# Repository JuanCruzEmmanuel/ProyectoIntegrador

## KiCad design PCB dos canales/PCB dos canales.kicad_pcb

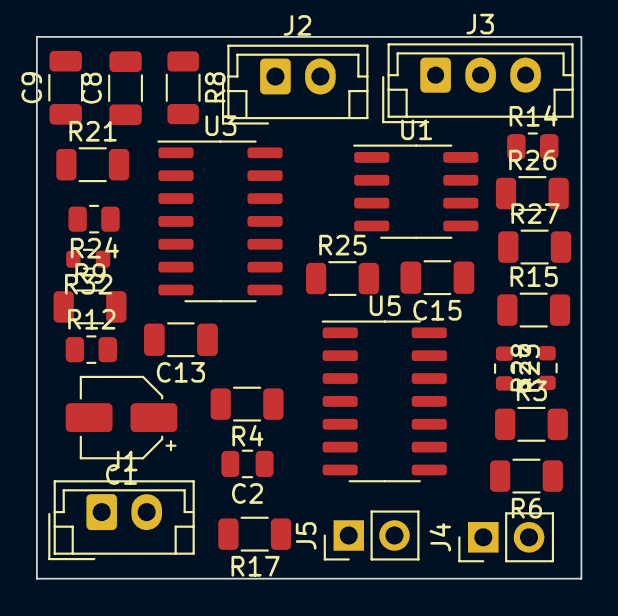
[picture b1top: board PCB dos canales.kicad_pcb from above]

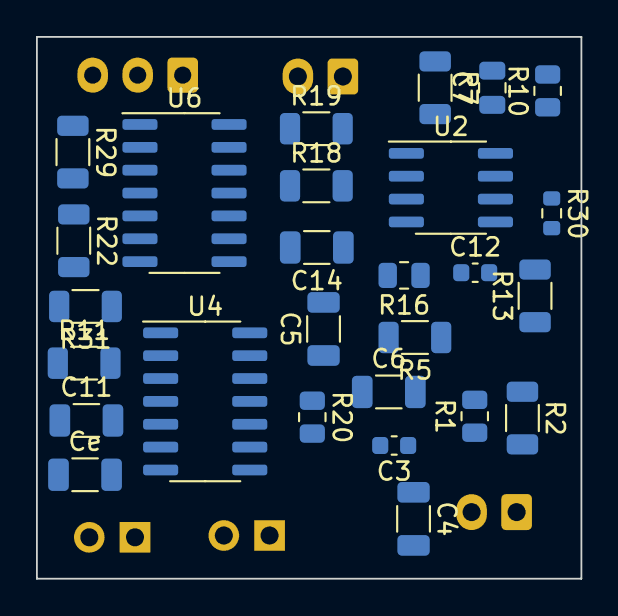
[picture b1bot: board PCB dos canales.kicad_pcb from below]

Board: 2 copper layers, 30.3 x 30.1 mm, 58 parts (27 on the bottom side), 45 nets, no tracks yet.

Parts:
C1: 47uF; CP_Elec_4x4.5
C2, C7: 47nF; C_0805_2012Metric
C3, C12: 100nF; C_0603_1608Metric
C4, C13: 220nF; C_1206_3216Metric
C5, C6, C8, C9: 1nF; C_1206_3216Metric
C11, C14, C15: 1uF; C_1206_3216Metric
Ce: 1uF; C_1206_3216Metric
J1, J2: Conn_01x02; JST_EH_B2B-EH-A_1x02_P2.50mm_Vertical
J3: Conn_01x03; JST_EH_B3B-EH-A_1x03_P2.50mm_Vertical
J4, J5: Conn_01x02; PinHeader_1x02_P2.54mm_Vertical
R1: 3.3M; R_0805_2012Metric
R2: 2.2M; R_1206_3216Metric
R3, R6, R9, R13: 39K; R_1206_3216Metric
R4, R5, R7, R8, R17, R21: 4.7K; R_1206_3216Metric
R10, R14: 8K; R_0805_2012Metric
R11, R15, R25, R31: 1M; R_1206_3216Metric
R12, R16: 470K; R_0805_2012Metric
R18, R19, R26, R27: 100K; R_1206_3216Metric
R20, R24: 70K; R_0805_2012Metric
R22, R29: 560K; R_1206_3216Metric
R23, R28, R30, R32: 1.5K; R_0603_1608Metric
U1, U2: AD620; SOIC-8_3.9x4.9mm_P1.27mm
U3, U4, U5, U6: LM324; SO-14_3.9x8.65mm_P1.27mm

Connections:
+V: C1.1, J1.2, R1.1, U1.7 (Vs+), U2.7 (Vs+), U3.4 (V+), U4.4 (V+), U5.4 (V+), U6.4 (V+)
-V: C1.2, J1.1, J4.2, J5.2, R2.2, U1.4 (Vs-), U2.4 (Vs-), U3.11 (V-), U4.11 (V-), U5.11 (V-), U6.11 (V-)
ElecNegHor: J3.2, R7.1
ElecNegVer: J2.1, R4.1
ElecPositHor: J3.3, R8.1
ElecPositVer: J2.2, R5.1
GND: C3.1, C5.2, C6.2, C8.2, C9.2, C12.1, R11.1, R15.1, R17.2, R21.2, R23.1, R30.1, U1.5 (Ref), U2.5 (Ref), U4.1, U4.2 (-), U4.12 (+), U6.12 (+)
unnamed: C4.2, R3.2, R6.1
unnamed: C11.2, Ce.1, R12.2
unnamed: C13.2, R9.2, R13.1
unnamed: C14.1, C15.2, R16.2
unnamed: R1.2, R2.1, U4.3 (+)
unnamed: R30.2, R32.2, U3.9 (-)
unnamed: R21.1, R24.2, U3.2 (-)
unnamed: C15.1, R15.2, U3.5 (+)
unnamed: C12.2, R13.2, U3.12 (+)
unnamed: C13.1, C14.2, U3.13 (-), U3.14
unnamed: R26.2, R27.1, U4.5 (+)
unnamed: R29.2, U4.6 (-), U4.7, U4.13 (-)
unnamed: R31.1, U4.14
unnamed: R17.1, R20.2, U5.2 (-)
unnamed: C11.1, R11.2, U5.5 (+)
unnamed: R23.2, R28.2, U5.9 (-)
unnamed: C3.2, R6.2, U5.12 (+)
unnamed: C4.1, Ce.2, U5.13 (-), U5.14
unnamed: R18.2, R19.1, U6.5 (+)
unnamed: R22.2, U6.6 (-), U6.7, U6.13 (-)
unnamed: R25.1, U6.14
OUTHor1: U1.6, U3.3 (+)
OUTHor2: R9.1, R24.1, U3.1
OUTHor3: R16.1, U3.6 (-), U3.7, U3.10 (+)
OUTHor4: J5.1, R32.1, U3.8
OUTVer1: U2.6, U5.3 (+)
OUTVer2: R3.1, R20.1, U5.1
OUTVer3: R12.1, U5.6 (-), U5.7, U5.10 (+)
OUTVer4: J4.1, R28.1, U5.8
OutNegHor: C7.2, C8.1, R7.2, U1.2 (-)
OutNegVer: C2.2, C5.1, R4.2, U2.2 (-)
OutPositHor: C7.1, C9.1, R8.2, U1.3 (+)
OutPositVer: C2.1, C6.1, R5.2, U2.3 (+)
Ref: J3.1, R22.1, R25.2, R29.1, R31.2
RgHor1: R14.2, R26.1, U1.1 (Rg)
RgHor2: R14.1, R27.2, U1.8 (Rg)
RgVer1: R10.2, R18.1, U2.1 (Rg)
RgVer2: R10.1, R19.2, U2.8 (Rg)

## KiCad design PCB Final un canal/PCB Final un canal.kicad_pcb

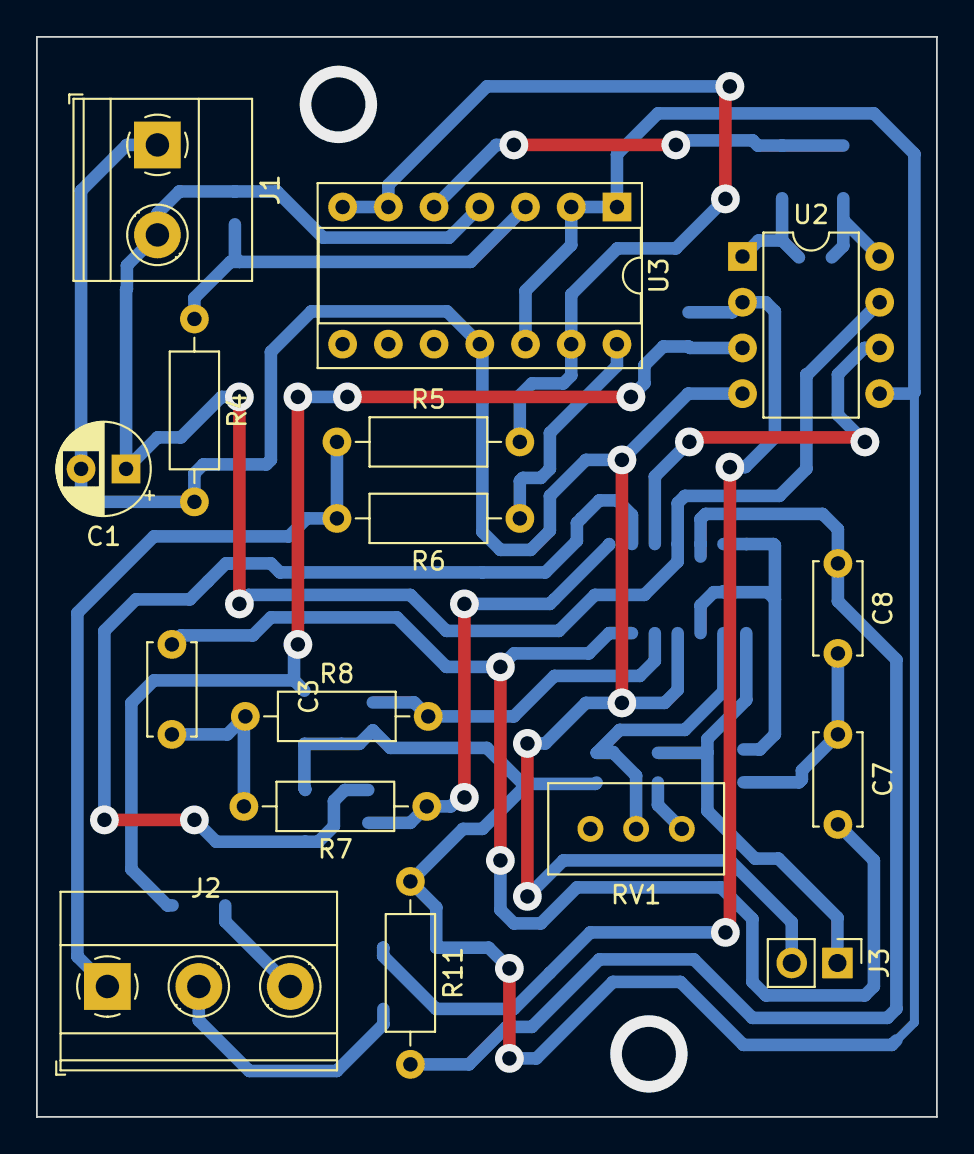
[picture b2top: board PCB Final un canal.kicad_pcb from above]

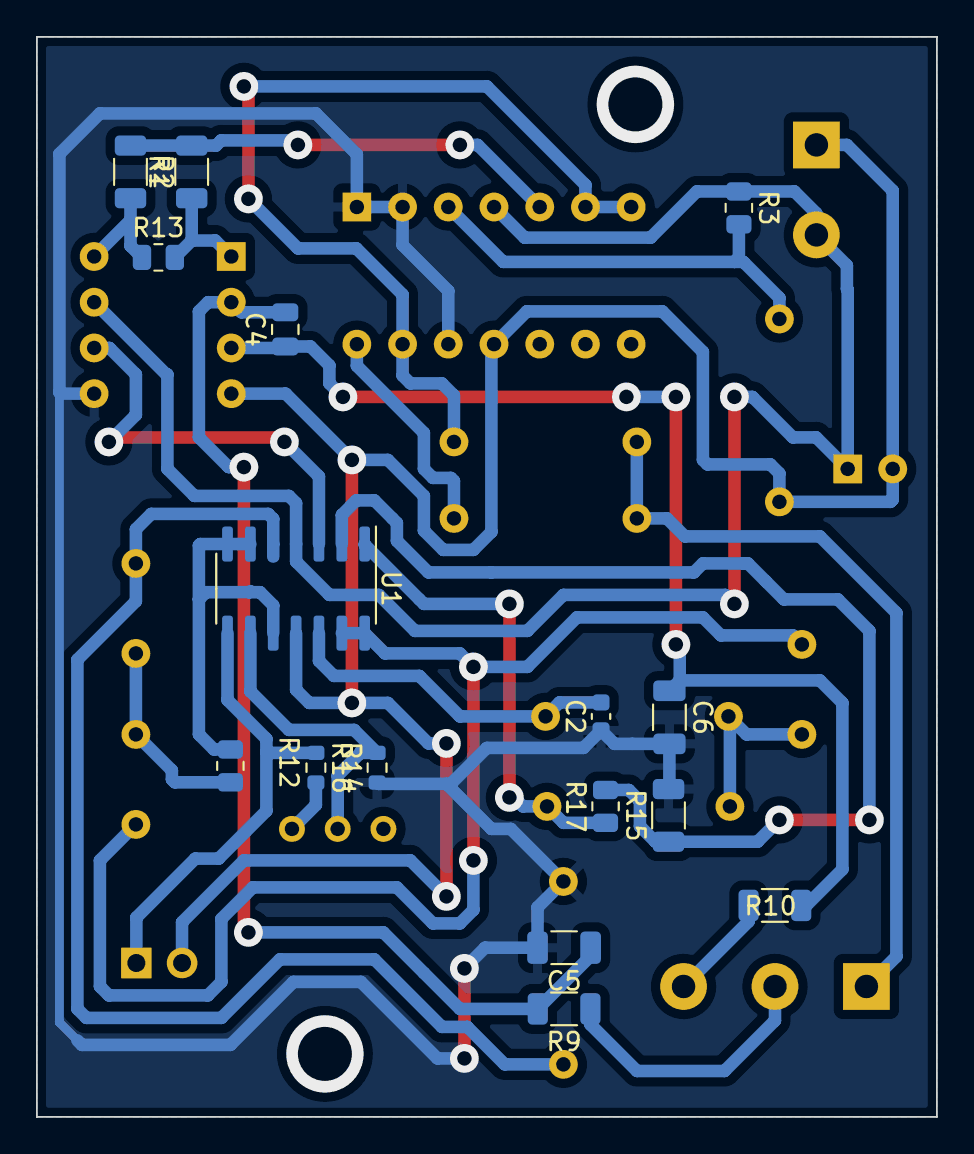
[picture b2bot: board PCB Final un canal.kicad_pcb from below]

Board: 2 copper layers, 50.0 x 60.0 mm, 32 parts (16 on the bottom side), 26 nets.

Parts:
C1: 47uF; CP_Radial_D5.0mm_P2.50mm
C2: 100nF; C_0603_1608Metric
C3: 220nF; C_Disc_D5.0mm_W2.5mm_P5.00mm
C4: 47nF; C_0805_2012Metric
C5, C6: 1nF; C_1206_3216Metric
C7, C8: 1uF; C_Disc_D5.0mm_W2.5mm_P5.00mm
J1: Conn_01x02; TerminalBlock_Phoenix_MKDS-1,5-2_1x02_P5.00mm_Horizontal
J2: Conn_01x03; TerminalBlock_Phoenix_MKDS-1,5-3-5.08_1x03_P5.08mm_Horizont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
J3: Conn_01x02; PinHeader_1x02_P2.54mm_Vertical
R1, R2: 100K; R_1206_3216Metric
R3: 3.3M; R_0805_2012Metric
R4: 2.2M; R_Axial_DIN0207_L6.3mm_D2.5mm_P10.16mm_Horizontal
R5: 560K; R_Axial_DIN0207_L6.3mm_D2.5mm_P10.16mm_Horizontal
R6, R11: 1M; R_Axial_DIN0207_L6.3mm_D2.5mm_P10.16mm_Horizontal
R7, R8: 39K; R_Axial_DIN0207_L6.3mm_D2.5mm_P10.16mm_Horizontal
R9, R10, R15: 4.7K; R_1206_3216Metric
R12: 470K; R_0805_2012Metric
R13: 8K; R_0805_2012Metric
R14, R16: 1.5K; R_0603_1608Metric
R17: 70K; R_0805_2012Metric
RV1: 100K; Potentiometer_Bourns_3296W_Vertical
U1: LM324; SO-14_3.9x8.65mm_P1.27mm
U2: AD620; DIP-8_W7.62mm
U3: LM324; DIP-14_W7.62mm_Socket

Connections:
+V: C1.1, J1.2, R3.1, U1.4 (V+), U2.7 (Vs+), U3.4 (V+)
-V: C1.2, J1.1, J3.2, R4.2, U1.11 (V-), U2.4 (Vs-), U3.11 (V-)
ElecNeg: J2.2, R9.1
ElecPosit: J2.3, R10.1
GND: C2.1, C5.2, C6.2, R11.1, R14.1, R15.2, U2.5 (Ref), U3.1, U3.2 (-), U3.12 (+)
unnamed: C2.2, R8.2, U1.12 (+)
unnamed: C3.1, C7.2, U1.13 (-), U1.14
unnamed: C3.2, R7.2, R8.1
unnamed: C7.1, C8.2, R12.2
unnamed: C8.1, R11.2, U1.5 (+)
unnamed: R1.2, R2.1, U3.5 (+)
unnamed: R3.2, R4.1, U3.3 (+)
unnamed: R5.2, U3.6 (-), U3.7, U3.13 (-)
unnamed: R6.1, U3.14
unnamed: R14.2, RV1.2, U1.9 (-)
unnamed: R15.1, R17.2, U1.2 (-)
unnamed: R16.2, RV1.3
OUT1: U1.3 (+), U2.6
OUT2: R7.1, R17.1, U1.1
OUT3: R12.1, U1.6 (-), U1.7, U1.10 (+)
OUT4: J3.1, R16.1, U1.8
OutNEg: C4.2, C5.1, R9.2, U2.2 (-)
OutPosit: C4.1, C6.1, R10.2, U2.3 (+)
Ref: J2.1, R5.1, R6.2
Rg1: R1.1, R13.2, U2.1 (Rg)
Rg2: R2.2, R13.1, U2.8 (Rg)

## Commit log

2022-05-13 primer commit
2022-05-20 Agrego la carpeta 3D Model
2022-05-20 Edite el banana Hembra que estaba en pulgadas
2022-05-21 Agrego carpeta con PCB Final sin terminar
2022-05-21 Agrego otros elementos a la carpeta 3d model
2022-05-21 Agrego la PCB con smd terminada de routear
2022-05-21 Sumo a mi git elementos de la pc de gustavo
2022-05-21 eliminando lo que me mande
2022-05-21 Subo este archivo de texto vacio
2022-05-21 Cambios para armar el master
2022-05-21 vuelvo a subir los archivos
2022-05-21 update pcb-gustavo
2022-05-22 Subo los avances de la PCB con ambos canales
2022-05-22 Se sube placas a imprimir
2022-05-23 Gustavo agrega cambios en la pcb dos canales
2022-05-23 Se agrega los .stl de los archivos a imprimir
2022-05-23 subo modificaciones a la carcasa con leyendas
2023-05-02 Trabajo final completo
